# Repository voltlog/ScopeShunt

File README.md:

# ScopeShunt
We usually use an oscilloscope for visualizing a voltage over time but sometimes it’s also useful to visualize the current waveform over time. The right way to do it is to get a current probe which can sense the current and convert that to a voltage that the oscilloscope can display however such devices are pretty expensive, they can be around $1000 even for an entry level one like the Rigol RP1001C which is only rated up to 300KHz bandwidth.

The ScopeShunt is actually just a pack of resistors connected in parallel to form a shunt resistor which is assembled neatly inside an aluminium enclosure complete with easy to use 4mm banana and BNC connectors. It can be used to visualise the current waveform on any oscilloscope. More info about the ScopeShunt in [Voltlog #310](https://www.youtube.com/watch?v=wDC6eQ25UTQ).

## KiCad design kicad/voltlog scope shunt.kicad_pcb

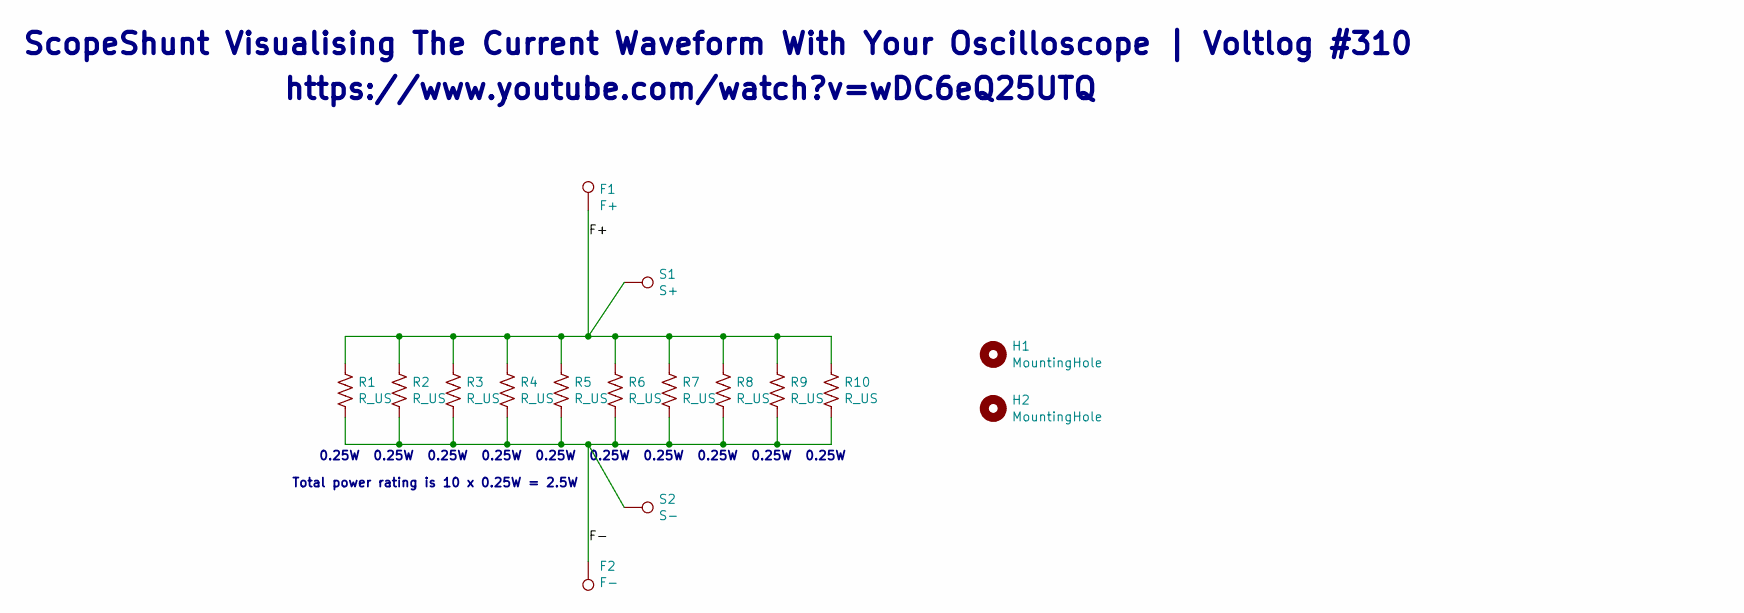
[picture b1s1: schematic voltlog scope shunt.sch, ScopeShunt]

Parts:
F1: F+; TestPoint_THTPad_D2.0mm_Drill1.0mm
F2: F-; TestPoint_THTPad_D2.0mm_Drill1.0mm
H1, H2: MountingHole; MountingHole_3.2mm_M3
R1, R2, R3, R4, R5, R6, R7, R8, R9, R10: R_US; R_1206_3216Metric
S1: S+; TestPoint_THTPad_D2.0mm_Drill1.0mm
S2: S-; TestPoint_THTPad_D2.0mm_Drill1.0mm

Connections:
/F+: F1.1, R1.1, R2.1, R3.1, R4.1, R5.1, R6.1, R7.1, R8.1, R9.1, R10.1, S1.1
/F-: F2.1, R1.2, R2.2, R3.2, R4.2, R5.2, R6.2, R7.2, R8.2, R9.2, R10.2, S2.1

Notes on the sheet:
0.25W
Total power rating is 10 x 0.25W = 2.5W
ScopeShunt Visualising The Current Waveform With Your Oscilloscope | Voltlog #310
https://www.youtube.com/watch?v=wDC6eQ25UTQ

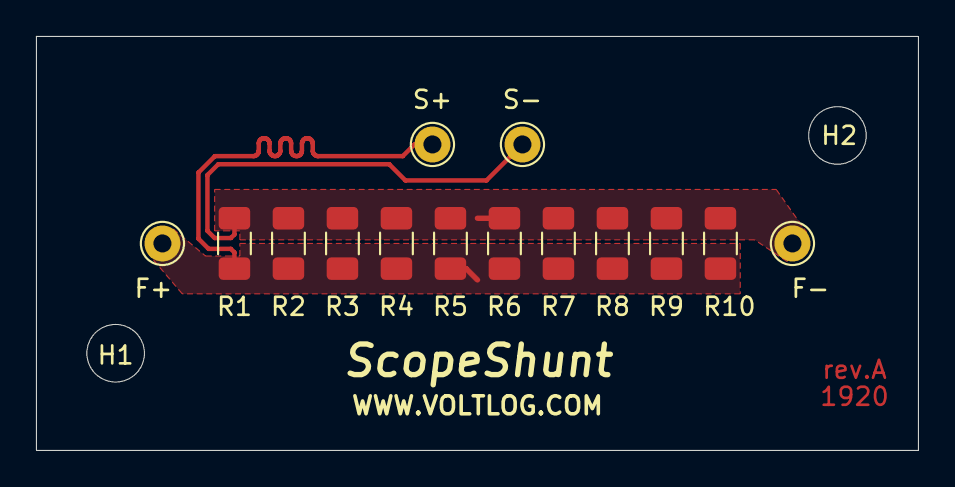
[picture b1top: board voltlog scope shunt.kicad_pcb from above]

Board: 2 copper layers, 49.0 x 23.0 mm, 16 parts (0 on the bottom side), 2 nets.

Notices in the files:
kicad/voltlog scope shunt.sch:
Released under GPLv2
